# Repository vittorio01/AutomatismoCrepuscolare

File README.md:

# AutomatismoCrepuscolare
Un automatismo crepuscolare programmabile e intelligente che può essere applicato in molti campi

La scheda funziona con un semplice arduino pro mini.

In questa pagina è presente, oltre a uno schema elettrico del circuito principale e il programma per l'atmega328, anche una guida per l'utilizzo e la costruzione.
Per chi volesse costruire la scheda elettronica, sul file bottom.pdf è predente la faccia inferiore (l'unica) gia pronta per essere utilizzata (da notare che vanno mssi anche due ponticelli.

Questo progetto è ancora in fase sperimentale, quindi c'è la possibilità che non funzioni correttamente.

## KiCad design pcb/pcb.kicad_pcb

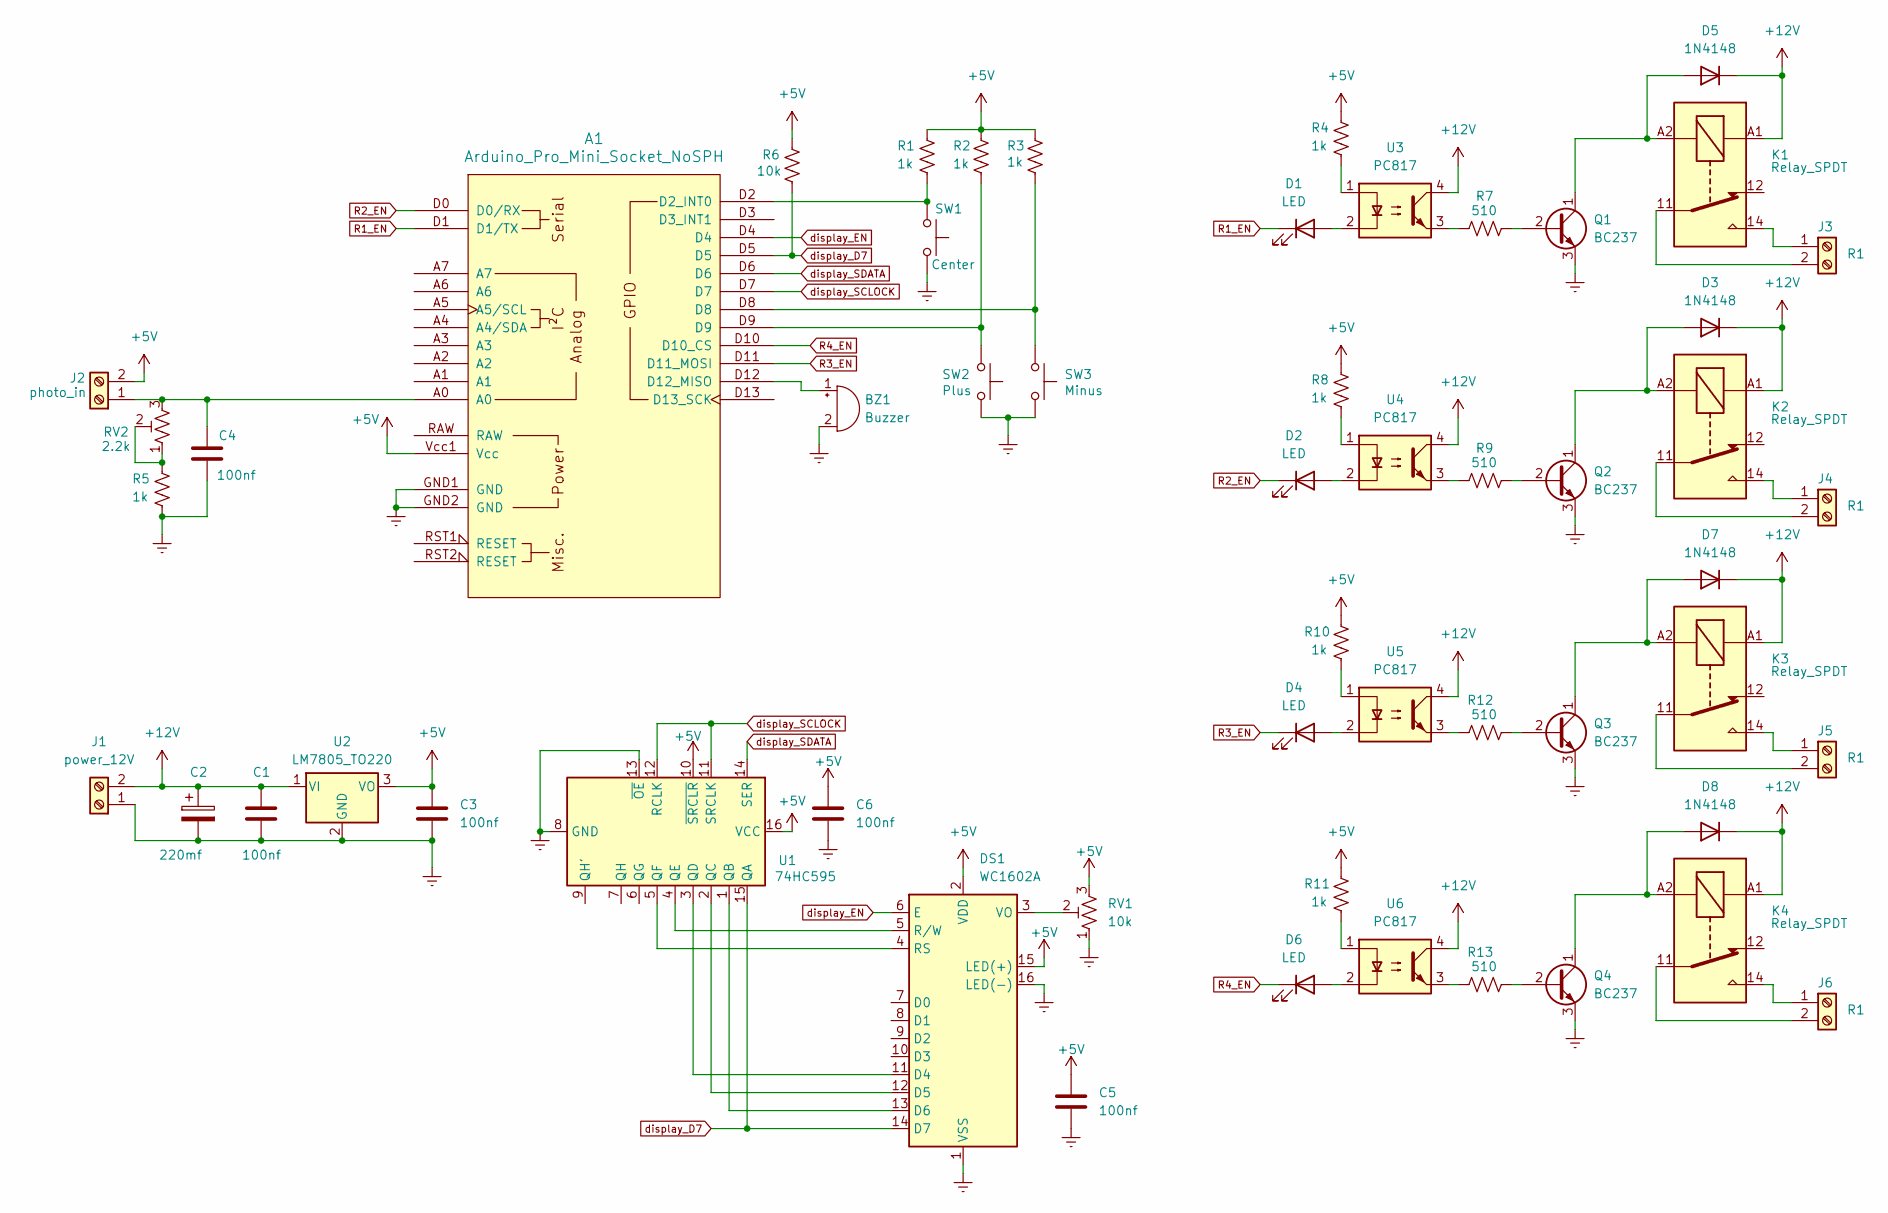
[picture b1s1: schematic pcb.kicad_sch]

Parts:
A1: Arduino_Pro_Mini_Socket_NoSPH
BZ1: Buzzer; Buzzer_15x7.5RM7.6
C1, C3, C4, C5, C6: 100nf; C_Rect_L7.2mm_W3.5mm_P5.00mm_FKS2_FKP2_MKS2_MKP2
C2: 220mf; C_Radial_D10.0mm_H12.5mm_P5.00mm
D1, D2, D4, D6: LED; LED_D5.0mm
D3, D5, D7, D8: 1N4148; D_DO-35_SOD27_P7.62mm_Horizontal
DS1: WC1602A; PinHeader_1x16_P2.54mm_Vertical
J1: power_12V; TerminalBlock_MaiXu_MX126-5.0-02P_1x02_P5.00mm
J2: photo_in; TerminalBlock_MaiXu_MX126-5.0-02P_1x02_P5.00mm
J3, J4, J5, J6: R1; TerminalBlock_MaiXu_MX126-5.0-02P_1x02_P5.00mm
K1, K2, K3, K4: Relay_SPDT; Relay_1-Form-C_Schrack-RYII_RM3.2mm
Q1, Q2, Q3, Q4: BC237; TO-92_Inline
R1, R2, R3, R4, R5, R8, R10, R11: 1k; R_Axial_DIN0207_L6.3mm_D2.5mm_P10.16mm_Horizontal
R6: 10k; R_Axial_DIN0207_L6.3mm_D2.5mm_P10.16mm_Horizontal
R7, R9, R12, R13: 510; R_Axial_DIN0207_L6.3mm_D2.5mm_P10.16mm_Horizontal
RV1: 10k; Potentiometer_Piher_PT-10-V10_Vertical
RV2: 2.2k; Potentiometer_Piher_PT-10-V10_Vertical
SW1: Center; PinHeader_1x02_P2.54mm_Vertical
SW2: Plus; PinHeader_1x02_P2.54mm_Vertical
SW3: Minus; PinHeader_1x02_P2.54mm_Vertical
U1: 74HC595; DIP-16_W7.62mm_Socket
U2: LM7805_TO220; TO-220-3_Vertical
U3, U4, U5, U6: PC817; DIP-4_W7.62mm

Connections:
+5V: A1.Vcc1 (Vcc), C3.1, C5.1, C6.1, DS1.2 (VDD), DS1.15 (LED(+)), J2.2, R1.1, R2.1, R3.1, R4.1, R6.1, R8.1, R10.1, R11.1, RV1.3, U1.10 (~SRCLR), U1.16 (VCC), U2.3 (VO)
+12V: C1.1, C2.1, D3.1 (K), D5.1 (K), D7.1 (K), D8.1 (K), J1.2, K1.A1, K2.A1, K3.A1, K4.A1, U2.1 (VI), U3.4, U4.4, U5.4, U6.4
GNDREF: A1.GND1 (GND), A1.GND2 (GND), BZ1.2 (-), C1.2, C2.2, C3.2, C4.2, C5.2, C6.2, DS1.1 (VSS), DS1.16 (LED(-)), J1.1, Q1.3 (E), Q2.3 (E), Q3.3 (E), Q4.3 (E), R5.2, RV1.1, SW1.2, SW2.2, SW3.2, U1.8 (GND), U1.13 (~OE), U2.2 (GND)
unnamed: A1.D2 (D2_INT0), R1.2, SW1.1
unnamed: A1.D12 (D12_MISO), BZ1.1 (+)
unnamed: A1.D8, R3.2, SW3.1
unnamed: A1.D9, R2.2, SW2.1
unnamed: D1.2 (A), U3.2
unnamed: D2.2 (A), U4.2
unnamed: D3.2 (A), K2.A2, Q2.1 (C)
unnamed: D4.2 (A), U5.2
unnamed: D5.2 (A), K1.A2, Q1.1 (C)
unnamed: D6.2 (A), U6.2
unnamed: D7.2 (A), K3.A2, Q3.1 (C)
unnamed: D8.2 (A), K4.A2, Q4.1 (C)
unnamed: DS1.11 (D4), U1.3 (QD)
unnamed: DS1.12 (D5), U1.2 (QC)
unnamed: DS1.13 (D6), U1.1 (QB)
unnamed: DS1.4 (RS), U1.5 (QF)
unnamed: DS1.5 (R/W), U1.4 (QE)
unnamed: DS1.3 (VO), RV1.2
unnamed: A1.A0, C4.1, J2.1, RV2.3
unnamed: J3.1, K1.14
unnamed: J3.2, K1.11
unnamed: J4.1, K2.14
unnamed: J4.2, K2.11
unnamed: J5.1, K3.14
unnamed: J5.2, K3.11
unnamed: J6.1, K4.14
unnamed: J6.2, K4.11
unnamed: Q1.2 (B), R7.2
unnamed: Q2.2 (B), R9.2
unnamed: Q3.2 (B), R12.2
unnamed: Q4.2 (B), R13.2
unnamed: R4.2, U3.1
unnamed: R5.1, RV2.1, RV2.2
unnamed: R7.1, U3.3
unnamed: R8.2, U4.1
unnamed: R9.1, U4.3
unnamed: R10.2, U5.1
unnamed: R11.2, U6.1
unnamed: R12.1, U5.3
unnamed: R13.1, U6.3
R1_EN: A1.D1 (D1/TX), D1.1 (K)
R2_EN: A1.D0 (D0/RX), D2.1 (K)
R3_EN: A1.D11 (D11_MOSI), D4.1 (K)
R4_EN: A1.D10 (D10_CS), D6.1 (K)
display_D7: A1.D5, DS1.14 (D7), R6.2, U1.15 (QA)
display_EN: A1.D4, DS1.6 (E)
display_SCLOCK: A1.D7, U1.11 (SRCLK), U1.12 (RCLK)
display_SDATA: A1.D6, U1.14 (SER)

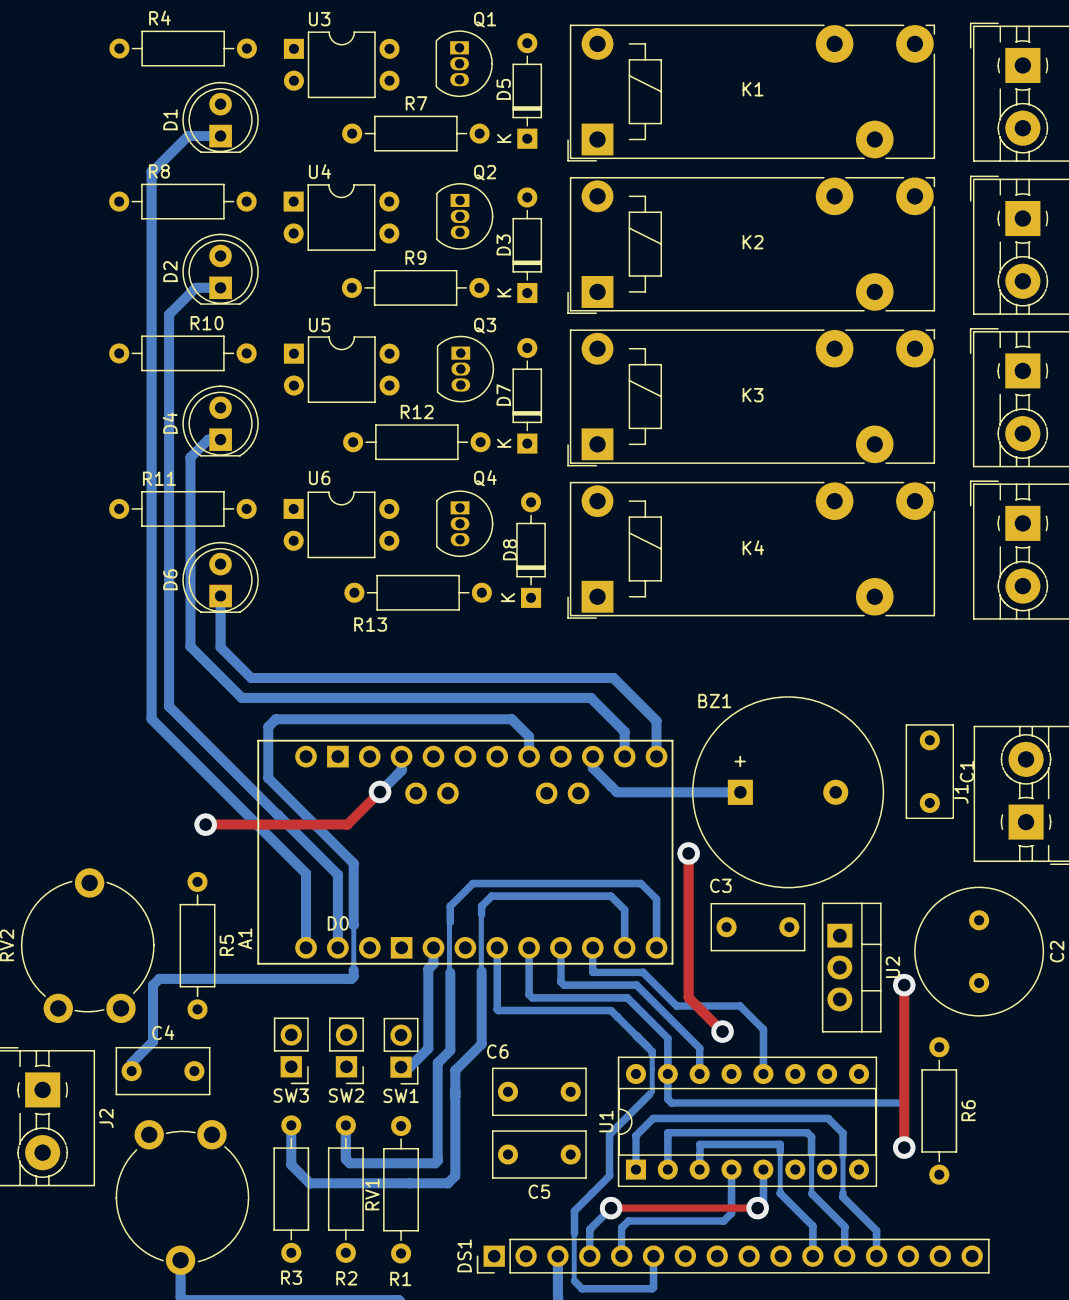
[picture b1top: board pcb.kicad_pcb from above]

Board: 2 copper layers, 55 parts (0 on the bottom side), 51 nets.

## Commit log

2025-01-14 aggiornato lo schema elettrico
2025-08-24 added base structure
2025-08-24 added lcd library
2025-08-25 added display class
2025-08-27 added display functions
2025-08-27 added functionalities
2025-08-29 addons
2025-09-05 added all functionalities
2025-09-05 bugfix
2025-09-05 optimizations
2025-09-05 refactoring progetto
